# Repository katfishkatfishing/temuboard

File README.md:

# temuboard

A compact 75% mechanical keyboard taken inspiration from the Keycool 84, that has a rotary encoder, and a small OLED display.

---

## Features

- **79 keys**
- **EC11 Rotary Encoder** - rotation bound to volume
- **128x64 I2C Display** - to play tiny animations
- **QMK firmware** - for STM32F405 MCUs
- **Bottom mount style** - Bottom case, plate, Cherry MX switches, top case

---

## Case Bottom

Case screws: M3

---

## Case Top

---

## Plate

1.5mm thickness

## Pin Mapping

| Function | Pin |
| --- | ---|
| Columns (col 1-15) | PA 0-2,6,7, PB 12-15, PC 4-9 |
| Row (row 1-6) | PA3, PB 0-2, 10,11 |
| Encoder A/B | PA8/PA10 |
| OLED SDA/SCL | PB6/PB7 |

---
## Firmware
- Uses QMK firmware
- Has only 1 layer
- Replaced right FN key to open task manager
- Programmed OLED display to play animations with 2 frames
- QMK firmware defaults rotary encoder to control volume
---
## PCB/Assembly Note
- All components are to be hand soldered, including SMD components
---
## Lessons learnt
- As a complete beginner to these things, I learnt so much about, planning out schematics, routing PCBs, and CAD. When I first started this project I didn't even know I had to make the keyboard layout. So, I had a friend of mine (thephantompx) that has more experience to guide me through the first few days of using Kicad and setting up the schematics. He gave me advice on the components needed, how to connect them, and also taught me how to route the PCB. We ran out of I/O pins on the Pico pi so we found a suitable MCU and made our own board. CAD was horrid. I used FreeCAD because OnShape was laggy for me. It took me 2 days to figure out how to even make a sketch, and the tutorial I was following didn't really teach too much of what I needed, just enough to get me started. Tbh I didn't think it'd take this long, but then again I started with literally 0 experience. This project was a great opportunity for me to use my free time to get experience on how to design things.

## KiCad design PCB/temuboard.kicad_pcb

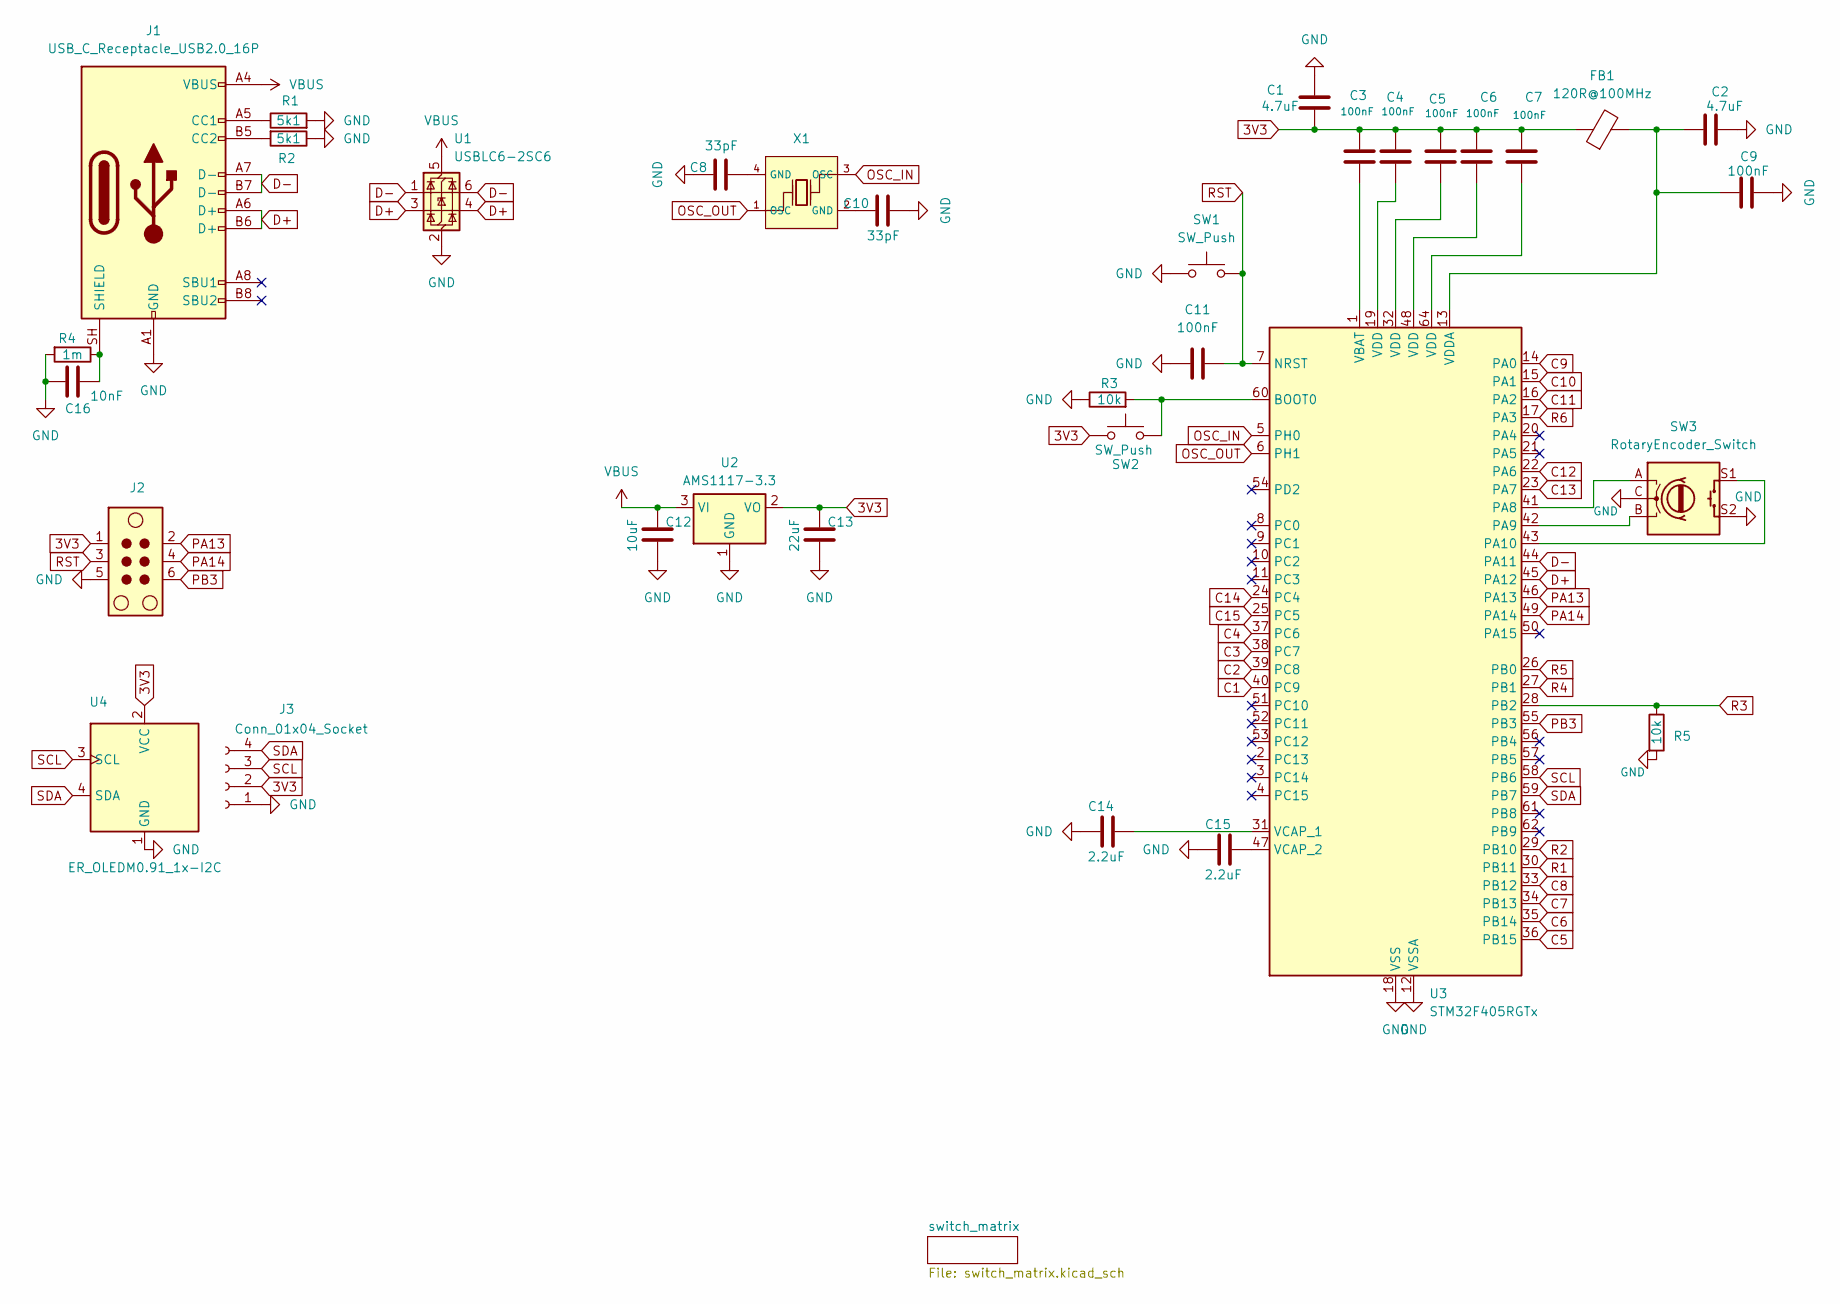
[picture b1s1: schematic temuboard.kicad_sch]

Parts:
C1, C2: 4.7uF; C_0805_2012Metric; LCSC Part # C98192
C3, C4, C5, C6, C7, C9, C11: 100nF; C_0201_0603Metric; LCSC Part # C76939
C8, C10: 33pF; C_0201_0603Metric; LCSC Part # C56903
C12: 10uF; C_0805_2012Metric; LCSC Part # C440198
C13: 22uF; C_0805_2012Metric; LCSC Part # C48986262
C14, C15: 2.2uF; C_0603_1608Metric; LCSC Part # C162273
C16: 10nF; C_0603_1608Metric; LCSC Part # C1589
FB1: 120R@100MHz; FB_0603; LCSC Part # C14709
J1: USB_C_Receptacle_USB2.0_16P; USB_C_Receptacle_GCT_USB4085; LCSC Part # C7095263
J2: TC2030; Tag-Connect_TC2030-IDC-NL_2x03_P1.27mm_Vertical
J3: Conn_01x04_Socket; PinSocket_1x04_P2.54mm_Vertical
R1, R2: 5k1; R_0603_1608Metric_Pad0.98x0.95mm_HandSolder
R3: 10k; R_0603_1608Metric_Pad0.98x0.95mm_HandSolder
R4: 1m; R_0603_1608Metric_Pad0.98x0.95mm_HandSolder
R5: 10k; C_0603_1608Metric_Pad1.08x0.95mm_HandSolder
SW1, SW2: SW_Push; SW_SPST_B3U-1000P; LCSC Part # C231329
SW3: RotaryEncoder_Switch; RotaryEncoder_Alps_EC11E-Switch_Vertical_H20mm
U1: USBLC6-2SC6; SOT-23-6; LCSC Part # C2687116
U2: AMS1117-3.3; SOT-223-3_TabPin2; LCSC Part # C351784
U3: STM32F405RGTx; LQFP-64_10x10mm_P0.5mm; LCSC Part # C15742
U4: ER_OLEDM0.91_1x-I2C
X1: X322525MOB4SI; OSC-SMD_4P-L3.2-W2.5-BL; Frequency Tolerance ±10ppm; Part X322525MOB4SI; LCSC C9006

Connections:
3V3: C1.2, C3.1, C4.2, C5.1, C6.2, C7.2, C13.1, FB1.1, J2.1, J3.2, SW2.1, U2.2 (VO), U4.2 (VCC)
C1: U3.40 (PC9); also elsewhere on the board
C2: U3.39 (PC8); also elsewhere on the board
C3: U3.38 (PC7); also elsewhere on the board
C4: U3.37 (PC6); also elsewhere on the board
C5: U3.36 (PB15); also elsewhere on the board
C6: U3.35 (PB14); also elsewhere on the board
C7: U3.34 (PB13); also elsewhere on the board
C8: U3.33 (PB12); also elsewhere on the board
C9: U3.14 (PA0); also elsewhere on the board
C10: U3.15 (PA1); also elsewhere on the board
C11: U3.16 (PA2); also elsewhere on the board
C12: U3.22 (PA6); also elsewhere on the board
C13: U3.23 (PA7); also elsewhere on the board
C14: U3.24 (PC4); also elsewhere on the board
C15: U3.25 (PC5); also elsewhere on the board
D+: J1.A6 (D+), J1.B6 (D+), U1.3 (I/O2), U1.4 (I/O2), U3.45 (PA12)
D-: J1.A7 (D-), J1.B7 (D-), U1.1 (I/O1), U1.6 (I/O1), U3.44 (PA11)
GND: C1.1, C2.1, C8.1, C9.1, C10.2, C11.1, C12.2, C13.2, C14.1, C15.1, C16.1, J1.A1 (GND), J1.A12 (GND), J1.B1 (GND), J1.B12 (GND), J2.5, J3.1, R1.2, R2.1, R3.1, R4.2, R5.2, SW1.1, SW3.C, SW3.S2, U1.2 (GND), U2.1 (GND), U3.12 (VSSA), U3.18 (VSS), U3.63 (VSS), U4.1 (GND)
unnamed: C4.1, U3.19 (VDD)
unnamed: C5.2, U3.32 (VDD)
unnamed: C6.1, U3.48 (VDD)
unnamed: C7.1, U3.64 (VDD)
unnamed: C8.2, X1.4 (GND)
unnamed: C10.1, X1.2 (GND)
unnamed: J1.A5 (CC1), R1.1
unnamed: J1.B5 (CC2), R2.2
unnamed: C16.2, J1.SH (SHIELD), R4.1
unnamed: R3.2, SW2.2, U3.60 (BOOT0)
unnamed: SW3.A, U3.41 (PA8)
unnamed: SW3.B, U3.42 (PA9)
unnamed: SW3.S1, U3.43 (PA10)
unnamed: C3.2, U3.1 (VBAT)
unnamed: C14.2, U3.31 (VCAP_1)
unnamed: C15.2, U3.47 (VCAP_2)
unnamed: C2.2, C9.2, FB1.2, U3.13 (VDDA)
OSC_IN: U3.5 (PH0), X1.3 (OSC)
OSC_OUT: U3.6 (PH1), X1.1 (OSC)
PA13: J2.2, U3.46 (PA13)
PA14: J2.4, U3.49 (PA14)
PB3: J2.6, U3.55 (PB3)
R1: U3.30 (PB11); also elsewhere on the board
R2: U3.29 (PB10); also elsewhere on the board
R3: R5.1, U3.28 (PB2); also elsewhere on the board
R4: U3.27 (PB1); also elsewhere on the board
R5: U3.26 (PB0); also elsewhere on the board
R6: U3.17 (PA3); also elsewhere on the board
RST: C11.2, J2.3, SW1.2, U3.7 (NRST)
SCL: J3.3, U3.58 (PB6), U4.3 (SCL)
SDA: J3.4, U3.59 (PB7), U4.4 (SDA)
VBUS: C12.1, J1.A4 (VBUS), J1.A9 (VBUS), J1.B4 (VBUS), J1.B9 (VBUS), U1.5 (VBUS), U2.3 (VI)

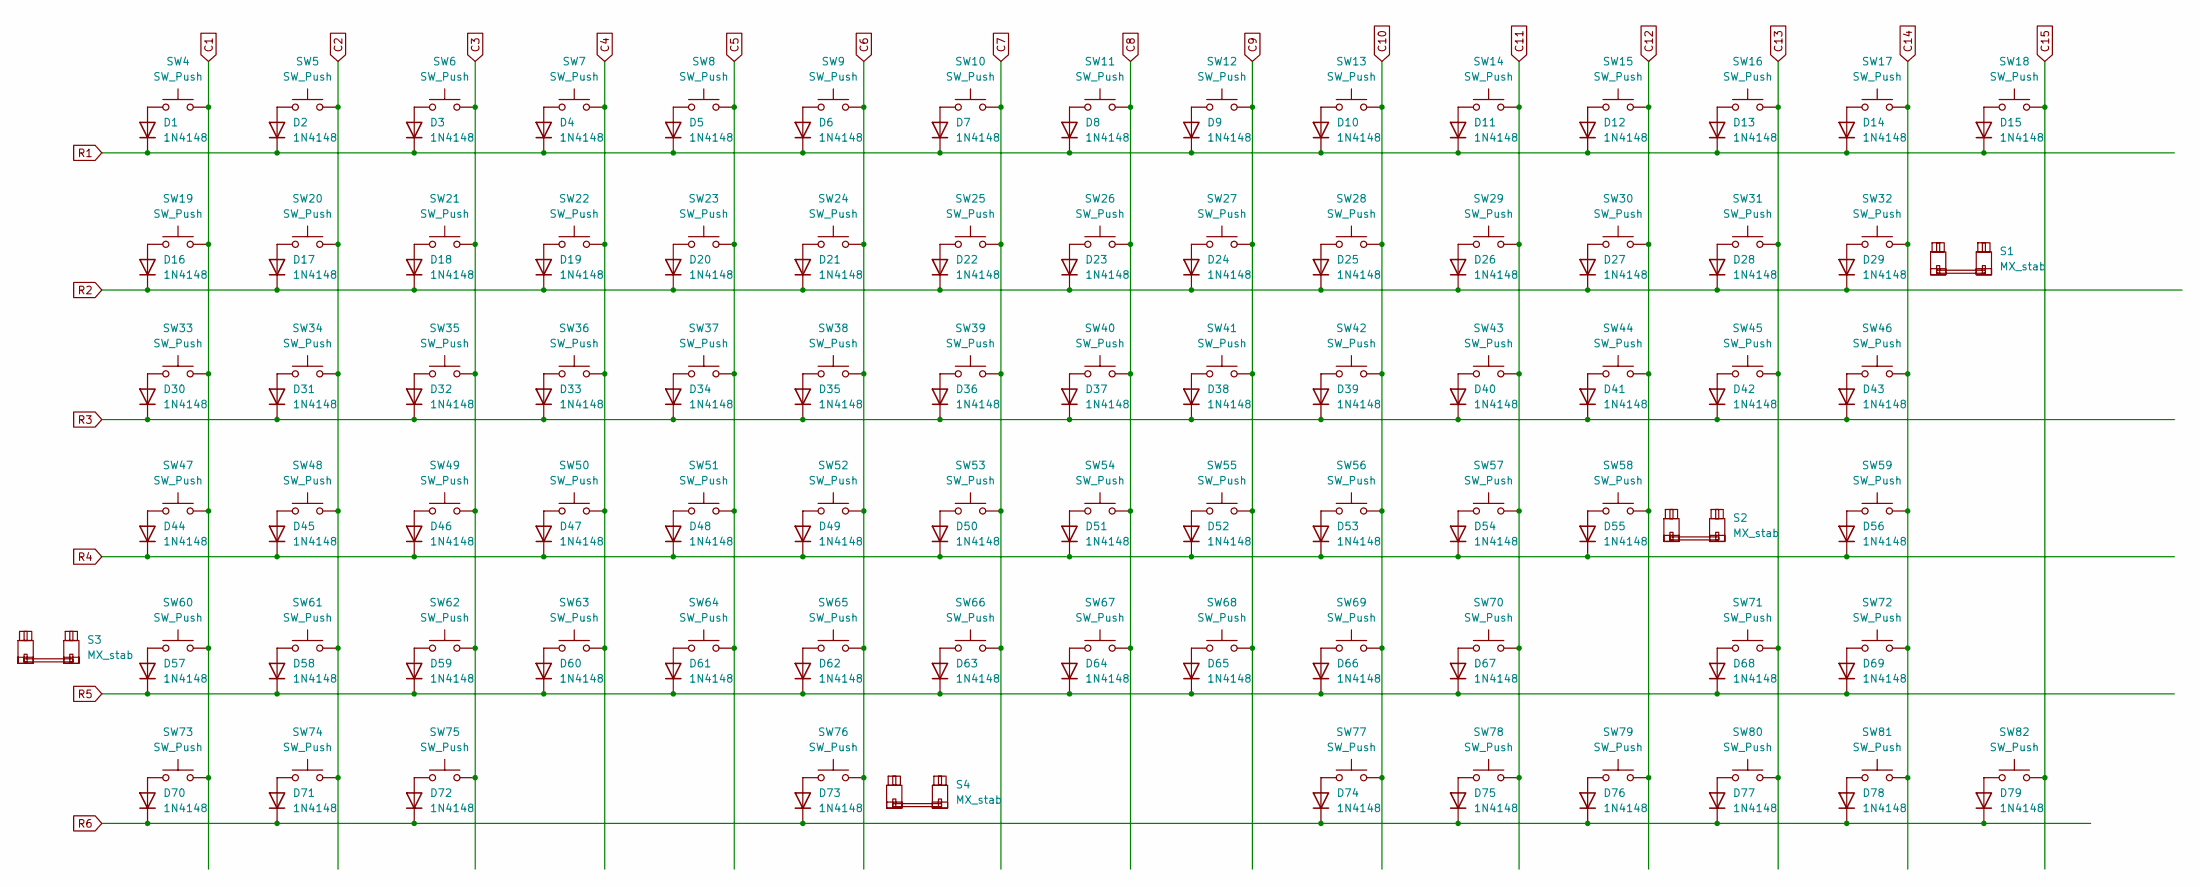
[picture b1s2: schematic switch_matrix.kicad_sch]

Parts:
D1, D2, D3, D4, D5, D6, D7, D8, D9, D10, D11, D12, D13, D14, D15, D16, D17, D18, D19, D20, D21, D22, D23, D24, D25, D26, D27, D28, D29, D30, D31, D32, D33, D34, D35, D36, D37, D38, D39, D40, D41, D42, D43, D44, D45, D46, D47, D48, D49, D50, D51, D52, D53, D54, D55, D56, D57, D58, D59, D60, D61, D62, D63, D64, D65, D66, D67, D68, D69, D70, D71, D72, D73, D74, D75, D76, D77, D78, D79: 1N4148; D_DO-35_SOD27_P7.62mm_Horizontal
S1: MX_stab; STAB_MX_P_2u
S2, S3: MX_stab; STAB_MX_P_2.25u
S4: MX_stab; STAB_MX_P_6.25u
SW4, SW5, SW6, SW7, SW8, SW9, SW10, SW11, SW12, SW13, SW14, SW15, SW16, SW17, SW18, SW19, SW20, SW21, SW22, SW23, SW24, SW25, SW26, SW27, SW28, SW29, SW30, SW31, SW32, SW33, SW34, SW35, SW36, SW37, SW38, SW39, SW40, SW41, SW42, SW43, SW44, SW45, SW46, SW47, SW48, SW49, SW50, SW51, SW52, SW53, SW54, SW55, SW56, SW57, SW58, SW59, SW60, SW61, SW62, SW63, SW64, SW65, SW66, SW67, SW68, SW69, SW70, SW71, SW72, SW73, SW74, SW75, SW76, SW77, SW78, SW79, SW80, SW81, SW82: SW_Push; SW_MX_HS_CPG151101S11_1u

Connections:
C1: SW4.2, SW19.2, SW33.2, SW47.2, SW60.2, SW73.2; also elsewhere on the board
C2: SW5.2, SW20.2, SW34.2, SW48.2, SW61.2, SW74.2; also elsewhere on the board
C3: SW6.2, SW21.2, SW35.2, SW49.2, SW62.2, SW75.2; also elsewhere on the board
C4: SW7.2, SW22.2, SW36.2, SW50.2, SW63.2; also elsewhere on the board
C5: SW8.2, SW23.2, SW37.2, SW51.2, SW64.2; also elsewhere on the board
C6: SW9.2, SW24.2, SW38.2, SW52.2, SW65.2, SW76.2; also elsewhere on the board
C7: SW10.2, SW25.2, SW39.2, SW53.2, SW66.2; also elsewhere on the board
C8: SW11.2, SW26.2, SW40.2, SW54.2, SW67.2; also elsewhere on the board
C9: SW12.2, SW27.2, SW41.2, SW55.2, SW68.2; also elsewhere on the board
C10: SW13.2, SW28.2, SW42.2, SW56.2, SW69.2, SW77.2; also elsewhere on the board
C11: SW14.2, SW29.2, SW43.2, SW57.2, SW70.2, SW78.2; also elsewhere on the board
C12: SW15.2, SW30.2, SW44.2, SW58.2, SW79.2; also elsewhere on the board
C13: SW16.2, SW31.2, SW45.2, SW71.2, SW80.2; also elsewhere on the board
C14: SW17.2, SW32.2, SW46.2, SW59.2, SW72.2, SW81.2; also elsewhere on the board
C15: SW18.2, SW82.2; also elsewhere on the board
unnamed: D1.2 (A), SW4.1
unnamed: D2.2 (A), SW5.1
unnamed: D3.2 (A), SW6.1
unnamed: D4.2 (A), SW7.1
unnamed: D5.2 (A), SW8.1
unnamed: D6.2 (A), SW9.1
unnamed: D7.2 (A), SW10.1
unnamed: D8.2 (A), SW11.1
unnamed: D9.2 (A), SW12.1
unnamed: D10.2 (A), SW13.1
unnamed: D11.2 (A), SW14.1
unnamed: D12.2 (A), SW15.1
unnamed: D13.2 (A), SW16.1
unnamed: D14.2 (A), SW17.1
unnamed: D15.2 (A), SW18.1
unnamed: D16.2 (A), SW19.1
unnamed: D17.2 (A), SW20.1
unnamed: D18.2 (A), SW21.1
unnamed: D19.2 (A), SW22.1
unnamed: D20.2 (A), SW23.1
unnamed: D21.2 (A), SW24.1
unnamed: D22.2 (A), SW25.1
unnamed: D23.2 (A), SW26.1
unnamed: D24.2 (A), SW27.1
unnamed: D25.2 (A), SW28.1
unnamed: D26.2 (A), SW29.1
unnamed: D27.2 (A), SW30.1
unnamed: D28.2 (A), SW31.1
unnamed: D29.2 (A), SW32.1
unnamed: D30.2 (A), SW33.1
unnamed: D31.2 (A), SW34.1
unnamed: D32.2 (A), SW35.1
unnamed: D33.2 (A), SW36.1
unnamed: D34.2 (A), SW37.1
unnamed: D35.2 (A), SW38.1
unnamed: D36.2 (A), SW39.1
unnamed: D37.2 (A), SW40.1
unnamed: D38.2 (A), SW41.1
unnamed: D39.2 (A), SW42.1
unnamed: D40.2 (A), SW43.1
unnamed: D41.2 (A), SW44.1
unnamed: D42.2 (A), SW45.1
unnamed: D43.2 (A), SW46.1
unnamed: D44.2 (A), SW47.1
unnamed: D45.2 (A), SW48.1
unnamed: D46.2 (A), SW49.1
unnamed: D47.2 (A), SW50.1
unnamed: D48.2 (A), SW51.1
unnamed: D49.2 (A), SW52.1
unnamed: D50.2 (A), SW53.1
unnamed: D51.2 (A), SW54.1
unnamed: D52.2 (A), SW55.1
unnamed: D53.2 (A), SW56.1
unnamed: D54.2 (A), SW57.1
unnamed: D55.2 (A), SW58.1
unnamed: D56.2 (A), SW59.1
unnamed: D57.2 (A), SW60.1
unnamed: D58.2 (A), SW61.1
unnamed: D59.2 (A), SW62.1
unnamed: D60.2 (A), SW63.1
unnamed: D61.2 (A), SW64.1
unnamed: D62.2 (A), SW65.1
unnamed: D63.2 (A), SW66.1
unnamed: D64.2 (A), SW67.1
unnamed: D65.2 (A), SW68.1
unnamed: D66.2 (A), SW69.1
unnamed: D67.2 (A), SW70.1
unnamed: D68.2 (A), SW71.1
unnamed: D69.2 (A), SW72.1
unnamed: D70.2 (A), SW73.1
unnamed: D71.2 (A), SW74.1
unnamed: D72.2 (A), SW75.1
unnamed: D73.2 (A), SW76.1
unnamed: D74.2 (A), SW77.1
unnamed: D75.2 (A), SW78.1
unnamed: D76.2 (A), SW79.1
unnamed: D77.2 (A), SW80.1
unnamed: D78.2 (A), SW81.1
unnamed: D79.2 (A), SW82.1
R1: D1.1 (K), D2.1 (K), D3.1 (K), D4.1 (K), D5.1 (K), D6.1 (K), D7.1 (K), D8.1 (K), D9.1 (K), D10.1 (K), D11.1 (K), D12.1 (K), D13.1 (K), D14.1 (K), D15.1 (K); also elsewhere on the board
R2: D16.1 (K), D17.1 (K), D18.1 (K), D19.1 (K), D20.1 (K), D21.1 (K), D22.1 (K), D23.1 (K), D24.1 (K), D25.1 (K), D26.1 (K), D27.1 (K), D28.1 (K), D29.1 (K); also elsewhere on the board
R3: D30.1 (K), D31.1 (K), D32.1 (K), D33.1 (K), D34.1 (K), D35.1 (K), D36.1 (K), D37.1 (K), D38.1 (K), D39.1 (K), D40.1 (K), D41.1 (K), D42.1 (K), D43.1 (K); also elsewhere on the board
R4: D44.1 (K), D45.1 (K), D46.1 (K), D47.1 (K), D48.1 (K), D49.1 (K), D50.1 (K), D51.1 (K), D52.1 (K), D53.1 (K), D54.1 (K), D55.1 (K), D56.1 (K); also elsewhere on the board
R5: D57.1 (K), D58.1 (K), D59.1 (K), D60.1 (K), D61.1 (K), D62.1 (K), D63.1 (K), D64.1 (K), D65.1 (K), D66.1 (K), D67.1 (K), D68.1 (K), D69.1 (K); also elsewhere on the board
R6: D70.1 (K), D71.1 (K), D72.1 (K), D73.1 (K), D74.1 (K), D75.1 (K), D76.1 (K), D77.1 (K), D78.1 (K), D79.1 (K); also elsewhere on the board

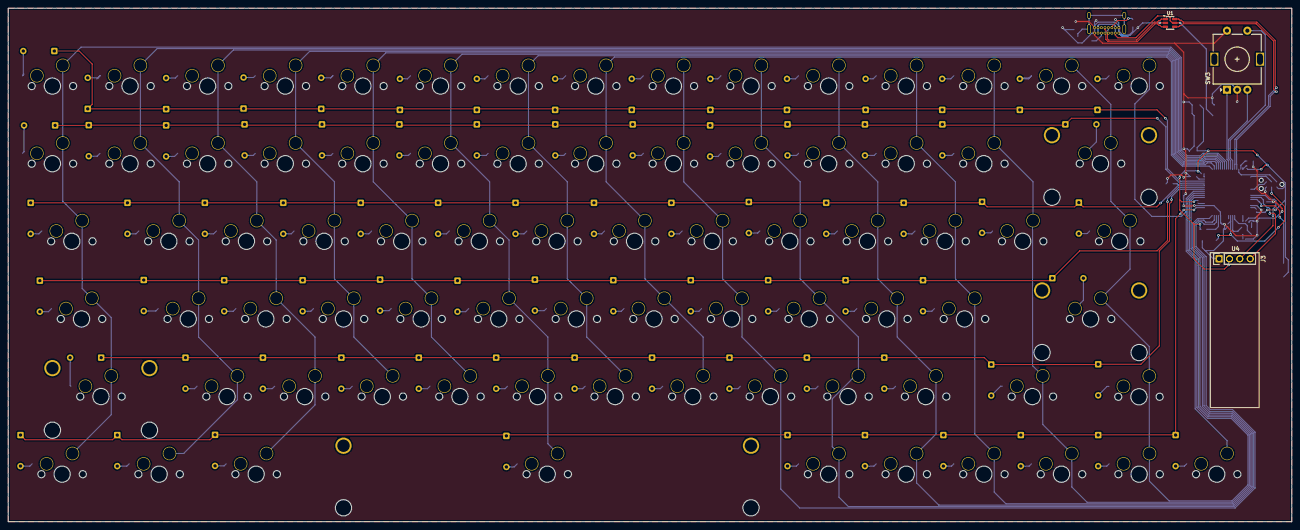
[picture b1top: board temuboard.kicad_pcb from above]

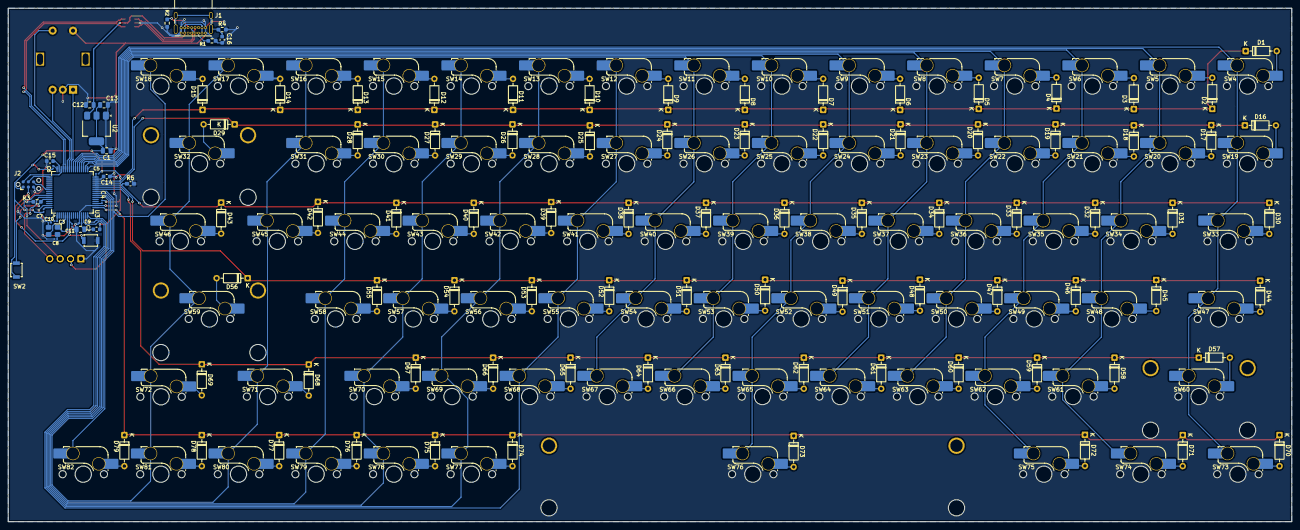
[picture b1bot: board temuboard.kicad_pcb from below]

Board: 2 copper layers, 315.0 x 126.0 mm, 195 parts (187 on the bottom side), 130 nets.

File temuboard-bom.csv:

Item,Parts,Qty,Price(USD),Link
Ceramic capacitor,10nF 0603,1,0.81,https://www.aliexpress.com/item/1005007137284660.html?spm=a2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
Ceramic capacitor,4.7uF 0805,2,1.61,https://www.aliexpress.com/item/1005007533370902.html?spm=a2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
Ceramic capacitor,100nF 0201,7,2.97,https://www.aliexpress.com/item/1005005961370114.html?spm=a2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
Ceramic capacitor,33pF 0201,2,0.60,https://www.aliexpress.com/item/1005008331136790.html?spm=a2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
Ceramic capacitor,10uF 0805,1,1.92,https://www.aliexpress.com/item/1005007533370902.html?spm=a2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
Ceramic capacitor,22uF 0805,1,2.22,https://www.aliexpress.com/item/1005007533370902.html?spm=a2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
Ceramic capacitor,2.2uF 0603,2,2.26,https://www.aliexpress.com/item/1005012364450156.html?spm=a2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
Diode,1N4148 SOD27,79,1.63,https://www.aliexpress.com/item/1005009379098965.html?spm=a2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
Ferrite Bead,120R@100MHz 0603,1,1.04,https://www.aliexpress.com/item/1005009841998170.html?spm=a2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
USB C RECEPTACLE,USB4085,1,6.26,https://www.aliexpress.com/item/1005010442732661.html?spm=a2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
Connector Pin Socket,PinSocket_1x04_P2.54mm_Vertical,1,3.27,https://www.aliexpress.com/item/1005004122312694.html?spm=a2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
Resistor,R_0603_1608Metric_Pad0.98x0.95mm_HandSolder 5k1,2,0.3,https://www.aliexpress.com/item/1005008628279880.html?spm=a2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
Resistor,R_0603_1608Metric_Pad0.98x0.95mm_HandSolder 1m,1,2.05,https://www.aliexpress.com/item/1005011779883974.html?spm=a2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
Resistor,R_0603_1608Metric_Pad0.98x0.95mm_HandSolder 10k,1,0.3,https://www.aliexpress.com/item/1005008628279880.html?spm=a2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
MX Stablizer,2u,1,0.99,https://www.aliexpress.com/item/1005006969058970.html?spm=a2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
MX Stablizer,2.25u,2,0.99,https://www.aliexpress.com/item/1005006969058970.html?spm=a2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
MX Stabilizer,6.25u,1,0.99,https://www.aliexpress.com/item/1005006969058970.html?spm=a2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
Button,SW_SPST_B3U-1000P,2,0.16,https://www.aliexpress.com/item/1005008817464692.html?spm=a2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
Rotary Encoder Switch,EC11,1,0.06,https://www.alibaba.com/product-detail/EC11-rotary-15-20mm-M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
Cherry MX Switch,Cherry MX Brown,79,11.83,https://www.aliexpress.com/item/1005002378701948.html?gatewa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
ESD Protection Diode,USBLC6-2SC6,1,3.13,https://www.aliexpress.com/item/1005007348100430.html?spm=a2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
Linear Regulator,AMS1117-3.3,1,0.60,https://www.aliexpress.com/item/1005009000664335.html?spm=a2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
Microcontroller,STM32F405RGT6,1,3.15,https://www.aliexpress.com/item/4000117720745.html?spm=a2g0o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
0.91 inch OLED Display,SSD1306,1,1.20,https://www.aliexpress.com/item/32836691660.html?gatewayAdap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
Crystal Oscillator,X322525MOB4SI,1,1.50,https://www.aliexpress.com/item/1005008501683836.html?spm=a2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
Keycaps,Cherry MX hiragana Keycaps,79,37.49,https://www.aliexpress.com/item/1005006113224623.html?spm=a2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
Rotary Encoder Knob,D-shaft 15mmx10mm,1,1.49,https://www.aliexpress.com/item/1005005751465974.html?spm=a2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
